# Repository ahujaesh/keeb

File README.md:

Eshaan's Split Keeb!

A seed studio rp2040 based ergonomic split keyboards to make essay writing slightly less boring! It has 50 keys (alphabet [26], numbers [10], ;,./ [4], two shifts [2], two ctrls [2], win key [1], two space keys [2], and two keys i plan to remap once the board comes in depending on what i fell like im missing), a built in USB hub, and a haptic motor!

PCB ([kicad](/keeb), [gerbers](/gerbers_final^2.zip)):

CAD ([STEP file of assembly](/final_assembly.step), [top plate](/Top%20plate.step), [bottom plate](/Bottom%20plate.step)):

Firmware [[left](/left.py), [right](/right.py)]: KMK (python), two files, one per board. Key matrix and one layer (for now, once i get the keeb i might add one more for funzies)
Aliexpress screenshot 

aliexpress screenshot with everything: 
amazon switches screenshot

All for the low price of 54.73 USD :crying emoji:

AND it has a built in USB hub for PIZZAZ

Using the USB2512_AEZG chip, I take an input of USBC and split it into two USBA ports (bc no laptop nowadays comes with USBA ports smh)

This keyboard has a 5x5 matrix on both sides, positioned at a comfortable 27 degrees so that my wrists don't cramp up while typing! It uses MX switches (the cheapest ones I could find lmao) (not hot swappable unfortunately), and 3d printed keycaps (save hack club some money lmao)

Finally, it has a built in haptic motor soldered onto the pcb to provide a better typing experience :) I couldnt find a cad model but its a really small motor that sits under the USBA ports and gets attached to the test points on the side of the seed studio

Note: switches are soldered on, I am printing the top and bottom plate, as well as the keycaps. for more info, see the [BOM](/bom.csv)

I had a lot of fun playing with splines etc whilst doing this project! Thanks hack club for the opportunity

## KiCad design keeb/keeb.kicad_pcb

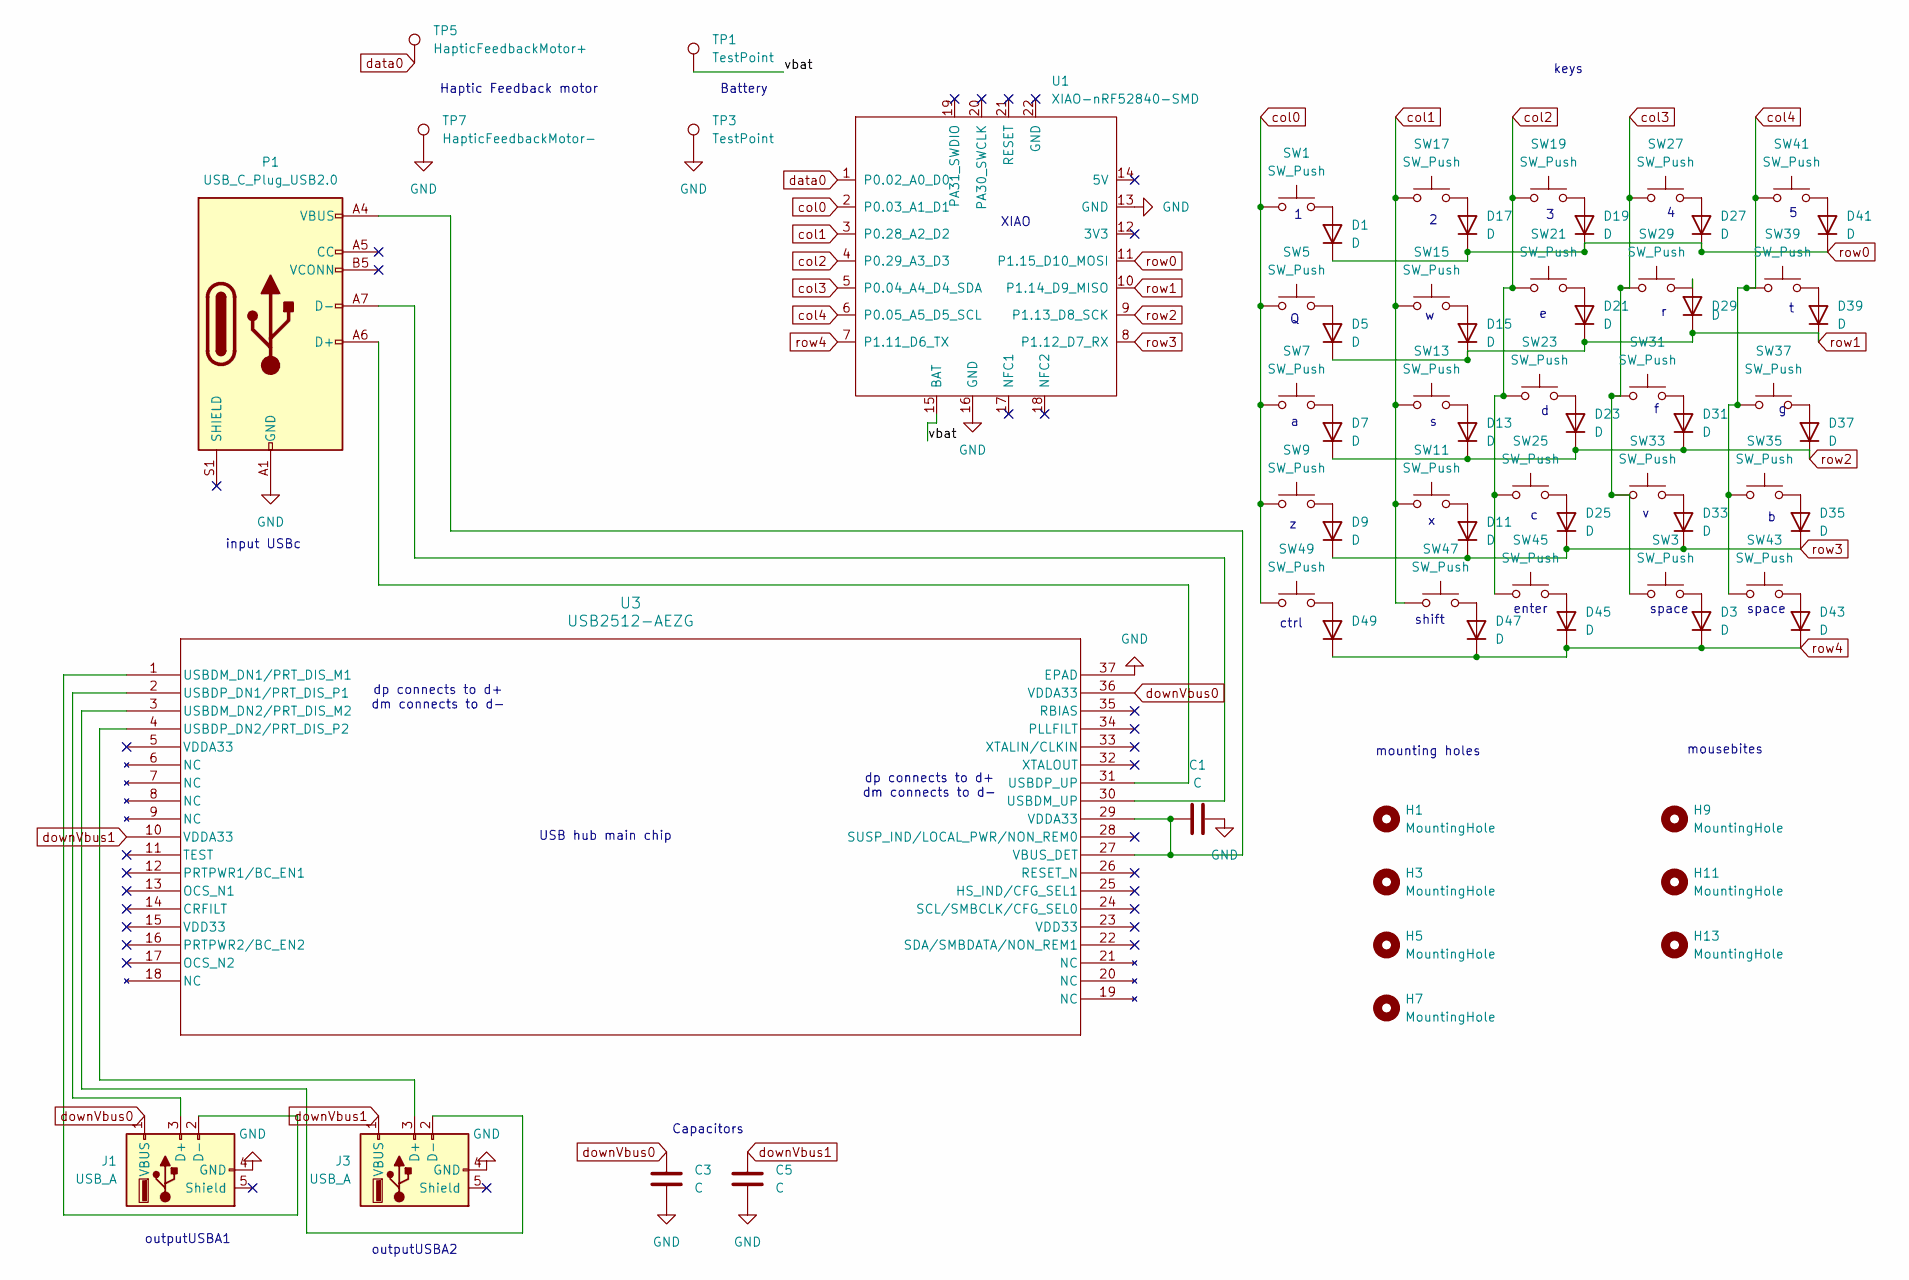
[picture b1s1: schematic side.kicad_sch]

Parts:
C1, C3, C5: C; CP_Axial_L11.0mm_D8.0mm_P15.00mm_Horizontal
D1, D3, D5, D7, D9, D11, D13, D15, D17, D19, D21, D23, D25, D27, D29, D31, D33, D35, D37, D39, D41, D43, D45, D47, D49: D; D_SOD-123
H1, H3, H5, H7: MountingHole; TestPoint_Loop_D3.80mm_Drill2.8mm
H9, H11, H13: MountingHole; mouse-bite-5mm-slot
J1, J3: USB_A; USB_A_Receptacle_GCT_USB1046
P1: USB_C_Plug_USB2.0; USB_C_Plug_Molex_105444
SW1, SW3, SW5, SW7, SW9, SW11, SW13, SW15, SW17, SW19, SW21, SW23, SW25, SW27, SW29, SW31, SW33, SW35, SW37, SW39, SW41, SW43, SW45, SW47, SW49: SW_Push; SW_Cherry_MX_1.00u_PCB
TP1, TP3: TestPoint; TestPoint_Pad_D3.0mm
TP5: HapticFeedbackMotor+; TestPoint_Pad_D4.0mm
TP7: HapticFeedbackMotor-; TestPoint_Pad_D4.0mm
U1: XIAO-nRF52840-SMD; modified-XIAO-nRF52840-SMD
U3: USB2512-AEZG; QFN36_6X6MC_MCH

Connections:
/left/vbat: TP1.1, U1.15 (BAT)
GND: C1.2, C3.2, C5.2, J1.4 (GND), J3.4 (GND), P1.A1 (GND), P1.A12 (GND), P1.B1 (GND), P1.B12 (GND), TP3.1, TP7.1, U1.13 (GND), U1.16 (GND), U3.37 (EPAD); also elsewhere on the board
unnamed: D1.2 (A), SW1.2
unnamed: D3.2 (A), SW3.2
unnamed: D5.2 (A), SW5.2
unnamed: D7.2 (A), SW7.2
unnamed: D9.2 (A), SW9.2
unnamed: D11.2 (A), SW11.2
unnamed: D13.2 (A), SW13.2
unnamed: D15.2 (A), SW15.2
unnamed: D17.2 (A), SW17.2
unnamed: D19.2 (A), SW19.2
unnamed: D21.2 (A), SW21.2
unnamed: D23.2 (A), SW23.2
unnamed: D25.2 (A), SW25.2
unnamed: D27.2 (A), SW27.2
unnamed: D29.2 (A), SW29.2
unnamed: D31.2 (A), SW31.2
unnamed: D33.2 (A), SW33.2
unnamed: D35.2 (A), SW35.2
unnamed: D37.2 (A), SW37.2
unnamed: D39.2 (A), SW39.2
unnamed: D41.2 (A), SW41.2
unnamed: D43.2 (A), SW43.2
unnamed: D45.2 (A), SW45.2
unnamed: D47.2 (A), SW47.2
unnamed: D49.2 (A), SW49.2
unnamed: J1.3 (D+), U3.2 (USBDP_DN1/PRT_DIS_P1)
unnamed: J1.2 (D-), U3.1 (USBDM_DN1/PRT_DIS_M1)
unnamed: J3.3 (D+), U3.4 (USBDP_DN2/PRT_DIS_P2)
unnamed: J3.2 (D-), U3.3 (USBDM_DN2/PRT_DIS_M2)
unnamed: P1.A6 (D+), U3.31 (USBDP_UP)
unnamed: P1.A7 (D-), U3.30 (USBDM_UP)
unnamed: C1.1, P1.A4 (VBUS), P1.A9 (VBUS), P1.B4 (VBUS), P1.B9 (VBUS), U3.27 (VBUS_DET), U3.29 (VDDA33)
col0: SW1.1, SW5.1, SW7.1, SW9.1, SW49.1, U1.2 (P0.03_A1_D1); also elsewhere on the board
col1: SW11.1, SW13.1, SW15.1, SW17.1, SW47.1, U1.3 (P0.28_A2_D2); also elsewhere on the board
col2: SW19.1, SW21.1, SW23.1, SW25.1, SW45.1, U1.4 (P0.29_A3_D3); also elsewhere on the board
col3: SW3.1, SW27.1, SW29.1, SW31.1, SW33.1, U1.5 (P0.04_A4_D4_SDA); also elsewhere on the board
col4: SW35.1, SW37.1, SW39.1, SW41.1, SW43.1, U1.6 (P0.05_A5_D5_SCL); also elsewhere on the board
data0: TP5.1, U1.1 (P0.02_A0_D0); also elsewhere on the board
downVbus0: C3.1, J1.1 (VBUS), U3.36 (VDDA33); also elsewhere on the board
downVbus1: C5.1, J3.1 (VBUS), U3.10 (VDDA33); also elsewhere on the board
row0: D1.1 (K), D17.1 (K), D19.1 (K), D27.1 (K), D41.1 (K), U1.11 (P1.15_D10_MOSI); also elsewhere on the board
row1: D5.1 (K), D15.1 (K), D21.1 (K), D29.1 (K), D39.1 (K), U1.10 (P1.14_D9_MISO); also elsewhere on the board
row2: D7.1 (K), D13.1 (K), D23.1 (K), D31.1 (K), D37.1 (K), U1.9 (P1.13_D8_SCK); also elsewhere on the board
row3: D9.1 (K), D11.1 (K), D25.1 (K), D33.1 (K), D35.1 (K), U1.8 (P1.12_D7_RX); also elsewhere on the board
row4: D3.1 (K), D43.1 (K), D45.1 (K), D47.1 (K), D49.1 (K), U1.7 (P1.11_D6_TX); also elsewhere on the board

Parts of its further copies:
C2, C4, C6: C; CP_Axial_L11.0mm_D8.0mm_P15.00mm_Horizontal
D2, D4, D6, D8, D10, D12, D14, D16, D18, D20, D22, D24, D26, D28, D30, D32, D34, D36, D38, D40, D42, D44, D46, D48, D50: D; D_SOD-123
H2, H4, H6, H8: MountingHole; TestPoint_Loop_D3.80mm_Drill2.8mm
H10, H12, H14: MountingHole; mouse-bite-5mm-slot
J2, J4: USB_A; USB_A_Receptacle_GCT_USB1046
SW2, SW4, SW6, SW8, SW10, SW12, SW14, SW16, SW18, SW20, SW22, SW24, SW26, SW28, SW30, SW32, SW34, SW36, SW38, SW40, SW42, SW44, SW46, SW48, SW50: SW_Push; SW_Cherry_MX_1.00u_PCB
U2: XIAO-nRF52840-SMD; modified-XIAO-nRF52840-SMD
U4: USB2512-AEZG; QFN36_6X6MC_MCH

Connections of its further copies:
/right/vbat: U2.15 (BAT); also elsewhere on the board
GND: C2.2, C4.2, C6.2, J2.4 (GND), J4.4 (GND), U2.13 (GND), U2.16 (GND), U4.37 (EPAD); also elsewhere on the board
unnamed: D2.2 (A), SW2.2
unnamed: D4.2 (A), SW4.2
unnamed: D6.2 (A), SW6.2
unnamed: D8.2 (A), SW8.2
unnamed: D10.2 (A), SW10.2
unnamed: D12.2 (A), SW12.2
unnamed: D14.2 (A), SW14.2
unnamed: D16.2 (A), SW16.2
unnamed: D18.2 (A), SW18.2
unnamed: D20.2 (A), SW20.2
unnamed: D22.2 (A), SW22.2
unnamed: D24.2 (A), SW24.2
unnamed: D26.2 (A), SW26.2
unnamed: D28.2 (A), SW28.2
unnamed: D30.2 (A), SW30.2
unnamed: D32.2 (A), SW32.2
unnamed: D34.2 (A), SW34.2
unnamed: D36.2 (A), SW36.2
unnamed: D38.2 (A), SW38.2
unnamed: D40.2 (A), SW40.2
unnamed: D42.2 (A), SW42.2
unnamed: D44.2 (A), SW44.2
unnamed: D46.2 (A), SW46.2
unnamed: D48.2 (A), SW48.2
unnamed: D50.2 (A), SW50.2
unnamed: J2.3 (D+), U4.2 (USBDP_DN1/PRT_DIS_P1)
unnamed: J2.2 (D-), U4.1 (USBDM_DN1/PRT_DIS_M1)
unnamed: J4.3 (D+), U4.4 (USBDP_DN2/PRT_DIS_P2)
unnamed: J4.2 (D-), U4.3 (USBDM_DN2/PRT_DIS_M2)
unnamed 63: U4.31 (USBDP_UP); also elsewhere on the board
unnamed 64: U4.30 (USBDM_UP); also elsewhere on the board
unnamed 66: C2.1, U4.27 (VBUS_DET), U4.29 (VDDA33); also elsewhere on the board
col0: SW2.1, SW6.1, SW8.1, SW10.1, SW50.1, U2.2 (P0.03_A1_D1); also elsewhere on the board
col1: SW12.1, SW14.1, SW16.1, SW18.1, SW48.1, U2.3 (P0.28_A2_D2); also elsewhere on the board
col2: SW20.1, SW22.1, SW24.1, SW26.1, SW46.1, U2.4 (P0.29_A3_D3); also elsewhere on the board
col3: SW4.1, SW28.1, SW30.1, SW32.1, SW34.1, U2.5 (P0.04_A4_D4_SDA); also elsewhere on the board
col4: SW36.1, SW38.1, SW40.1, SW42.1, SW44.1, U2.6 (P0.05_A5_D5_SCL); also elsewhere on the board
data0: U2.1 (P0.02_A0_D0); also elsewhere on the board
downVbus0: C4.1, J2.1 (VBUS), U4.36 (VDDA33); also elsewhere on the board
downVbus1: C6.1, J4.1 (VBUS), U4.10 (VDDA33); also elsewhere on the board
row0: D2.1 (K), D18.1 (K), D20.1 (K), D28.1 (K), D42.1 (K), U2.11 (P1.15_D10_MOSI); also elsewhere on the board
row1: D6.1 (K), D16.1 (K), D22.1 (K), D30.1 (K), D40.1 (K), U2.10 (P1.14_D9_MISO); also elsewhere on the board
row2: D8.1 (K), D14.1 (K), D24.1 (K), D32.1 (K), D38.1 (K), U2.9 (P1.13_D8_SCK); also elsewhere on the board
row3: D10.1 (K), D12.1 (K), D26.1 (K), D34.1 (K), D36.1 (K), U2.8 (P1.12_D7_RX); also elsewhere on the board
row4: D4.1 (K), D44.1 (K), D46.1 (K), D48.1 (K), D50.1 (K), U2.7 (P1.11_D6_TX); also elsewhere on the board

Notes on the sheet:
mousebites
dp connects to d+ dm connects to d-
enter
ctrl
input USBc
outputUSBA1
XIAO
shift
USB hub main chip
mounting holes
Battery
space
keys
Capacitors
outputUSBA2
Haptic Feedback motor

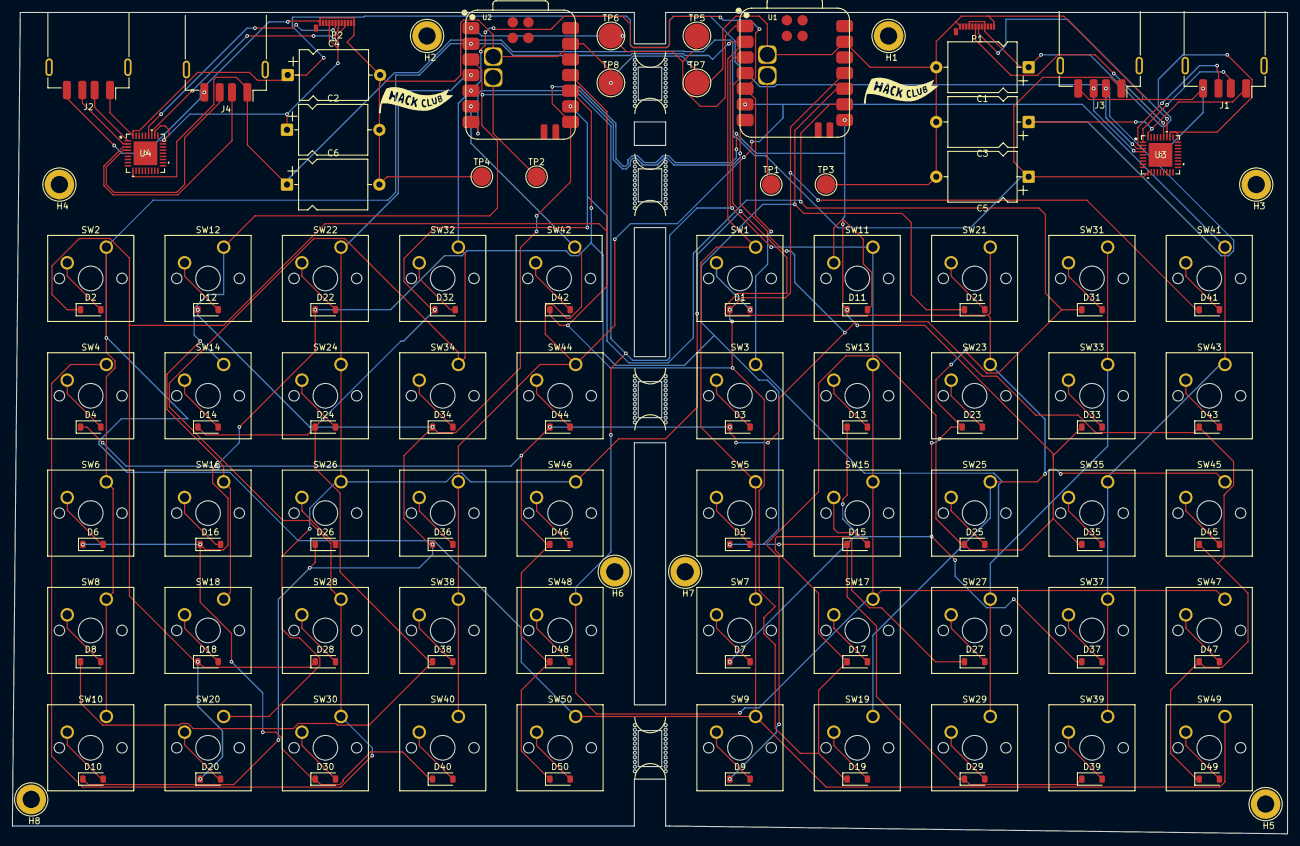
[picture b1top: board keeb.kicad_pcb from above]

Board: 2 copper layers, 207.0 x 133.3 mm, 136 parts (0 on the bottom side), 80 nets.

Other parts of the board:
P2: USB_C; USB_C_Plug_Molex_105444
TP2: Batt+; TestPoint_Pad_D3.0mm
TP4: Batt-; TestPoint_Pad_D3.0mm
TP6: Motor+; TestPoint_Pad_D4.0mm
TP8: Motor-; TestPoint_Pad_D4.0mm

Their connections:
/right/vbat: TP2.1; also elsewhere on the board
GND: P2.A1 (GND), P2.A12 (GND), P2.B1 (GND), P2.B12 (GND), TP4.1, TP8.1; also elsewhere on the board
unnamed 63: P2.A6 (D+); also elsewhere on the board
unnamed 64: P2.A7 (D-); also elsewhere on the board
unnamed 66: P2.A4 (VBUS), P2.A9 (VBUS), P2.B4 (VBUS), P2.B9 (VBUS); also elsewhere on the board
data0: TP6.1; also elsewhere on the board

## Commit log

2025-10-04 finished the schematic
2025-10-04 assigned footprints, fixed electrical rules checker errors
    I fixed the ERC errors by adding no connect flags to the unused pins, I assigned the footprints for all the components, and initialized the PCB with all the components. I also forgot to add the mount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
2025-10-04 misc kikad files spawned/despawned
2025-10-04 worked on routing
2025-10-05 finished routing, added the back Silkscreen, fixed DRC
    I finished the leftover routing, added some images to the back silkscreen, and went through the DRC errors. There are still some problems with the USB-C port's clearance, but otherwise, the PCB is al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
2025-10-05 gerbers
2025-10-07 fixed some pcbway errors
2025-10-08 cad stuff
2025-10-09 readme
2025-10-09 wrapped up project and made the BOM
2025-10-09 bom has to be lowercase lmao
2025-10-09 fix typo
